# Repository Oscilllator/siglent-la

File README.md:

# siglent-la

Forked and modified so that 4 ethernet cables are attached to the connector. The other end goes to two PMOD connectors concatenated together, which is part of the colorlight ecp5 fpga board

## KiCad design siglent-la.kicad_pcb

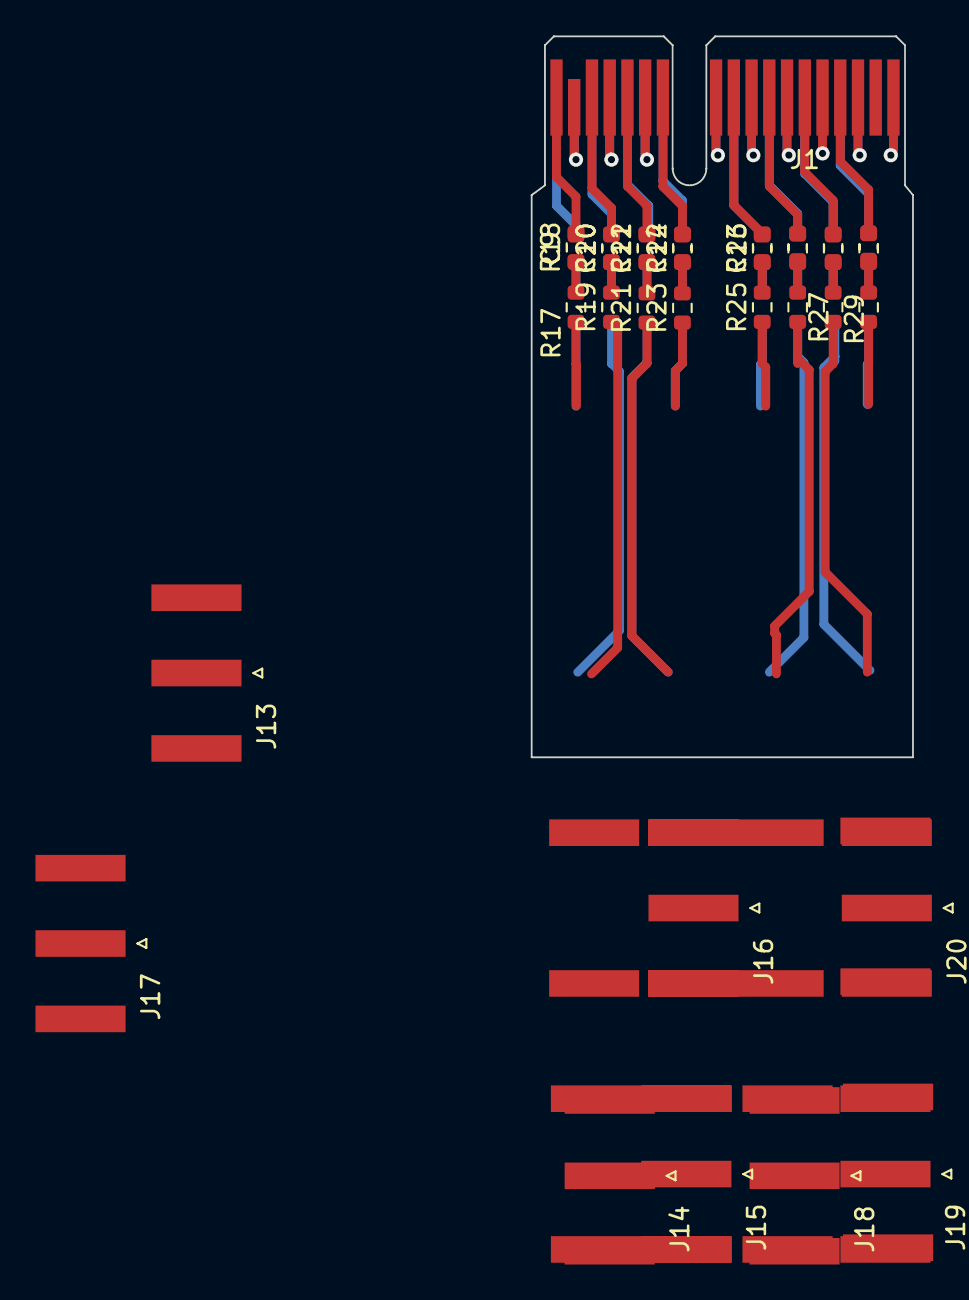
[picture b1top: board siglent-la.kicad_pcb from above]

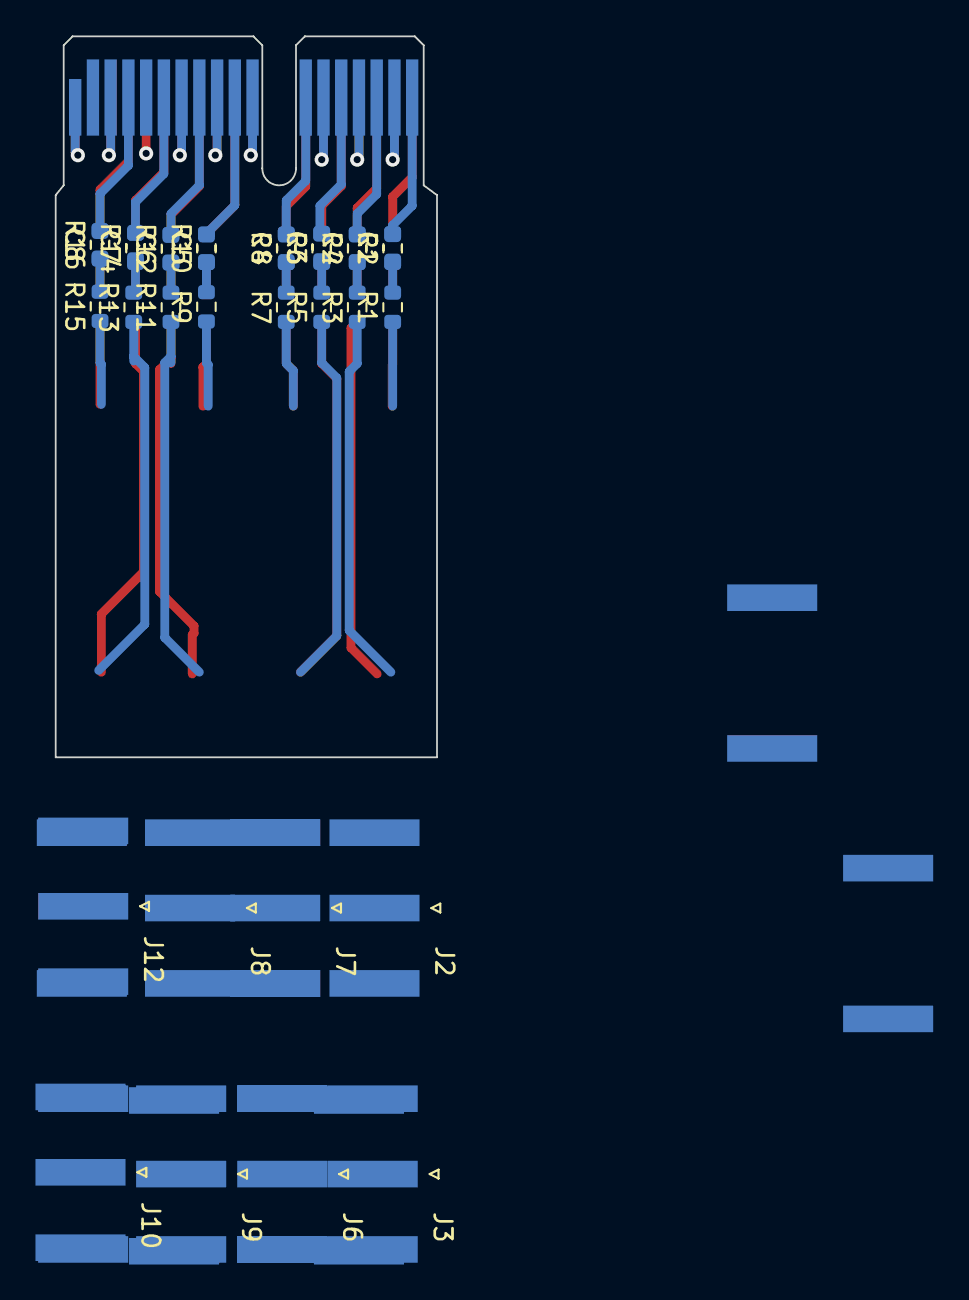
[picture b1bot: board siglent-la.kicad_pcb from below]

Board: 4 copper layers, 21.5 x 40.7 mm, 65 parts (32 on the bottom side), 49 nets.

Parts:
C1, C2, C3, C4, C5, C6, C7, C8, C9, C10, C11, C12, C13, C14, C15, C16: 8p2; C_0603_1608Metric
J1: Bus_PCI_Express_x1; BUS_PCIexpress_x1
J2, J3, J6, J7, J8, J9, J10, J12, J13, J14, J15, J16, J17, J18, J19, J20: IPEX-004; SMA_Amphenol_132289_EdgeMount
R1, R3, R5, R7, R9, R11, R13, R15, R17, R19, R21, R23, R25, R27, R29, R31: 120; R_0603_1608Metric
R2, R4, R6, R8, R10, R12, R14, R16, R18, R20, R22, R24, R26, R28, R30, R32: 91k; R_0603_1608Metric

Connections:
/input0/OUT: C1.2, J1.A18 (GND), R2.2
/input1/OUT: C2.2, J1.A16 (PERp0), R4.2
/input2/OUT: C3.2, J1.A14 (REFCLK-), R6.2
/input3/OUT: C4.2, J1.A12 (GND), R8.2
/input4/OUT: C5.2, J1.A10 (+3.3V), R10.2
/input5/OUT: C6.2, J1.A8 (JTAG5), R12.2
/input6/OUT: C7.2, J1.A6 (JTAG3), R14.2
/input7/OUT: C8.2, J1.A4 (GND), R16.2
/input8/OUT: C9.2, J1.B18 (GND), R18.2
/input9/OUT: C10.2, J1.B16 (GND), R20.2
/input10/OUT: C11.2, J1.B14 (PETp0), R22.2
/input11/OUT: C12.2, J1.B12 (RSVD), R24.2
/input12/OUT: C13.2, J1.B10 (3.3Vaux), R26.2
/input13/OUT: C14.2, J1.B8 (+3.3V), R28.2
/input14/OUT: C15.2, J1.B6 (SMDAT), R30.2
/input15/OUT: C16.2, J1.B4 (GND), R32.2
GND: J1.A1 (~PRSNT1), J1.A3 (+12V), J1.A5 (JTAG2), J1.A7 (JTAG4), J1.A9 (+3.3V), J1.A11 (~PERST), J1.A13 (REFCLK+), J1.A15 (GND), J1.A17 (PERn0), J1.B1 (+12V), J1.B3 (+12V), J1.B5 (SMCLK), J1.B7 (GND), J1.B9 (JTAG1), J1.B11 (~WAKE), J1.B13 (GND), J1.B15 (PETn0), J1.B17 (~PRSNT2), J2.2 (Ext), J3.2 (Ext), J6.2 (Ext), J7.2 (Ext), J8.2 (Ext), J9.2 (Ext), J10.2 (Ext), J12.2 (Ext), J13.2 (Ext), J14.2 (Ext), J15.2 (Ext), J16.2 (Ext), J17.2 (Ext), J18.2 (Ext), J19.2 (Ext), J20.2 (Ext)
unnamed: C1.1, R1.2, R2.1
unnamed: C2.1, R3.2, R4.1
unnamed: C3.1, R5.2, R6.1
unnamed: C4.1, R7.2, R8.1
unnamed: C5.1, R9.2, R10.1
unnamed: C6.1, R11.2, R12.1
unnamed: C7.1, R13.2, R14.1
unnamed: C8.1, R15.2, R16.1
unnamed: C9.1, R17.2, R18.1
unnamed: C10.1, R19.2, R20.1
unnamed: C11.1, R21.2, R22.1
unnamed: C12.1, R23.2, R24.1
unnamed: C13.1, R25.2, R26.1
unnamed: C14.1, R27.2, R28.1
unnamed: C15.1, R29.2, R30.1
unnamed: C16.1, R31.2, R32.1
unnamed: J2.1 (In), R1.1
unnamed: J3.1 (In), R3.1
unnamed: J6.1 (In), R5.1
unnamed: J7.1 (In), R7.1
unnamed: J8.1 (In), R9.1
unnamed: J9.1 (In), R11.1
unnamed: J10.1 (In), R13.1
unnamed: J12.1 (In), R15.1
unnamed: J13.1 (In), R17.1
unnamed: J14.1 (In), R19.1
unnamed: J15.1 (In), R21.1
unnamed: J16.1 (In), R23.1
unnamed: J17.1 (In), R25.1
unnamed: J18.1 (In), R27.1
unnamed: J19.1 (In), R29.1
unnamed: J20.1 (In), R31.1

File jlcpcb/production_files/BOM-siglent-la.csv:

Comment,Designator,Footprint,LCSC
91k,R30,R_0603_1608Metric,
120,R31,R_0603_1608Metric,
120,R21,R_0603_1608Metric,
91k,R20,R_0603_1608Metric,
8p2,C15,C_0603_1608Metric,
120,R19,R_0603_1608Metric,
120,R17,R_0603_1608Metric,
120,R23,R_0603_1608Metric,
91k,R24,R_0603_1608Metric,
91k,R32,R_0603_1608Metric,
120,R29,R_0603_1608Metric,
8p2,C9,C_0603_1608Metric,
8p2,C10,C_0603_1608Metric,
120,R25,R_0603_1608Metric,
8p2,C14,C_0603_1608Metric,
91k,R26,R_0603_1608Metric,
8p2,C11,C_0603_1608Metric,
8p2,C12,C_0603_1608Metric,
120,R27,R_0603_1608Metric,
91k,R22,R_0603_1608Metric,
91k,R28,R_0603_1608Metric,
8p2,C16,C_0603_1608Metric,
Bus_PCI_Express_x1,J1,BUS_PCIexpress_x1,
8p2,C13,C_0603_1608Metric,
91k,R18,R_0603_1608Metric,
91k,R16,R_0603_1608Metric,
91k,R10,R_0603_1608Metric,
8p2,C2,C_0603_1608Metric,
8p2,C8,C_0603_1608Metric,
120,R7,R_0603_1608Metric,
8p2,C5,C_0603_1608Metric,
120,R15,R_0603_1608Metric,
8p2,C3,C_0603_1608Metric,
120,R13,R_0603_1608Metric,
8p2,C6,C_0603_1608Metric,
91k,R8,R_0603_1608Metric,
120,R1,R_0603_1608Metric,
8p2,C4,C_0603_1608Metric,
91k,R12,R_0603_1608Metric,
91k,R6,R_0603_1608Metric,
120,R9,R_0603_1608Metric,
91k,R2,R_0603_1608Metric,
120,R5,R_0603_1608Metric,
8p2,C7,C_0603_1608Metric,
91k,R14,R_0603_1608Metric,
91k,R4,R_0603_1608Metric,
120,R11,R_0603_1608Metric,
120,R3,R_0603_1608Metric,
8p2,C1,C_0603_1608Metric,
IPEX-004,J20,U.FL_Molex_MCRF_73412-0110_Vertical,
IPEX-004,J19,U.FL_Molex_MCRF_73412-0110_Vertical,
IPEX-004,J18,U.FL_Molex_MCRF_73412-0110_Vertical,
IPEX-004,J17,U.FL_Molex_MCRF_73412-0110_Vertical,
IPEX-004,J16,U.FL_Molex_MCRF_73412-0110_Vertical,
IPEX-004,J15,U.FL_Molex_MCRF_73412-0110_Vertical,
IPEX-004,J14,U.FL_Molex_MCRF_73412-0110_Vertical,
IPEX-004,J13,U.FL_Molex_MCRF_73412-0110_Vertical,
IPEX-004,J12,U.FL_Molex_MCRF_73412-0110_Vertical,
IPEX-004,J10,U.FL_Molex_MCRF_73412-0110_Vertical,
IPEX-004,J9,U.FL_Molex_MCRF_73412-0110_Vertical,
IPEX-004,J8,U.FL_Molex_MCRF_73412-0110_Vertical,
IPEX-004,J7,U.FL_Molex_MCRF_73412-0110_Vertical,
IPEX-004,J6,U.FL_Molex_MCRF_73412-0110_Vertical,
IPEX-004,J3,U.FL_Molex_MCRF_73412-0110_Vertical,
IPEX-004,J2,U.FL_Molex_MCRF_73412-0110_Vertical,

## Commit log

2024-08-23 ufl connector
2024-10-05 rj45 version of the logic analyzer
2024-10-05 copy over the pmod connector for the colorlight fpga board
2024-10-27 commit after horrendous kicad bug that lost all my work :((
